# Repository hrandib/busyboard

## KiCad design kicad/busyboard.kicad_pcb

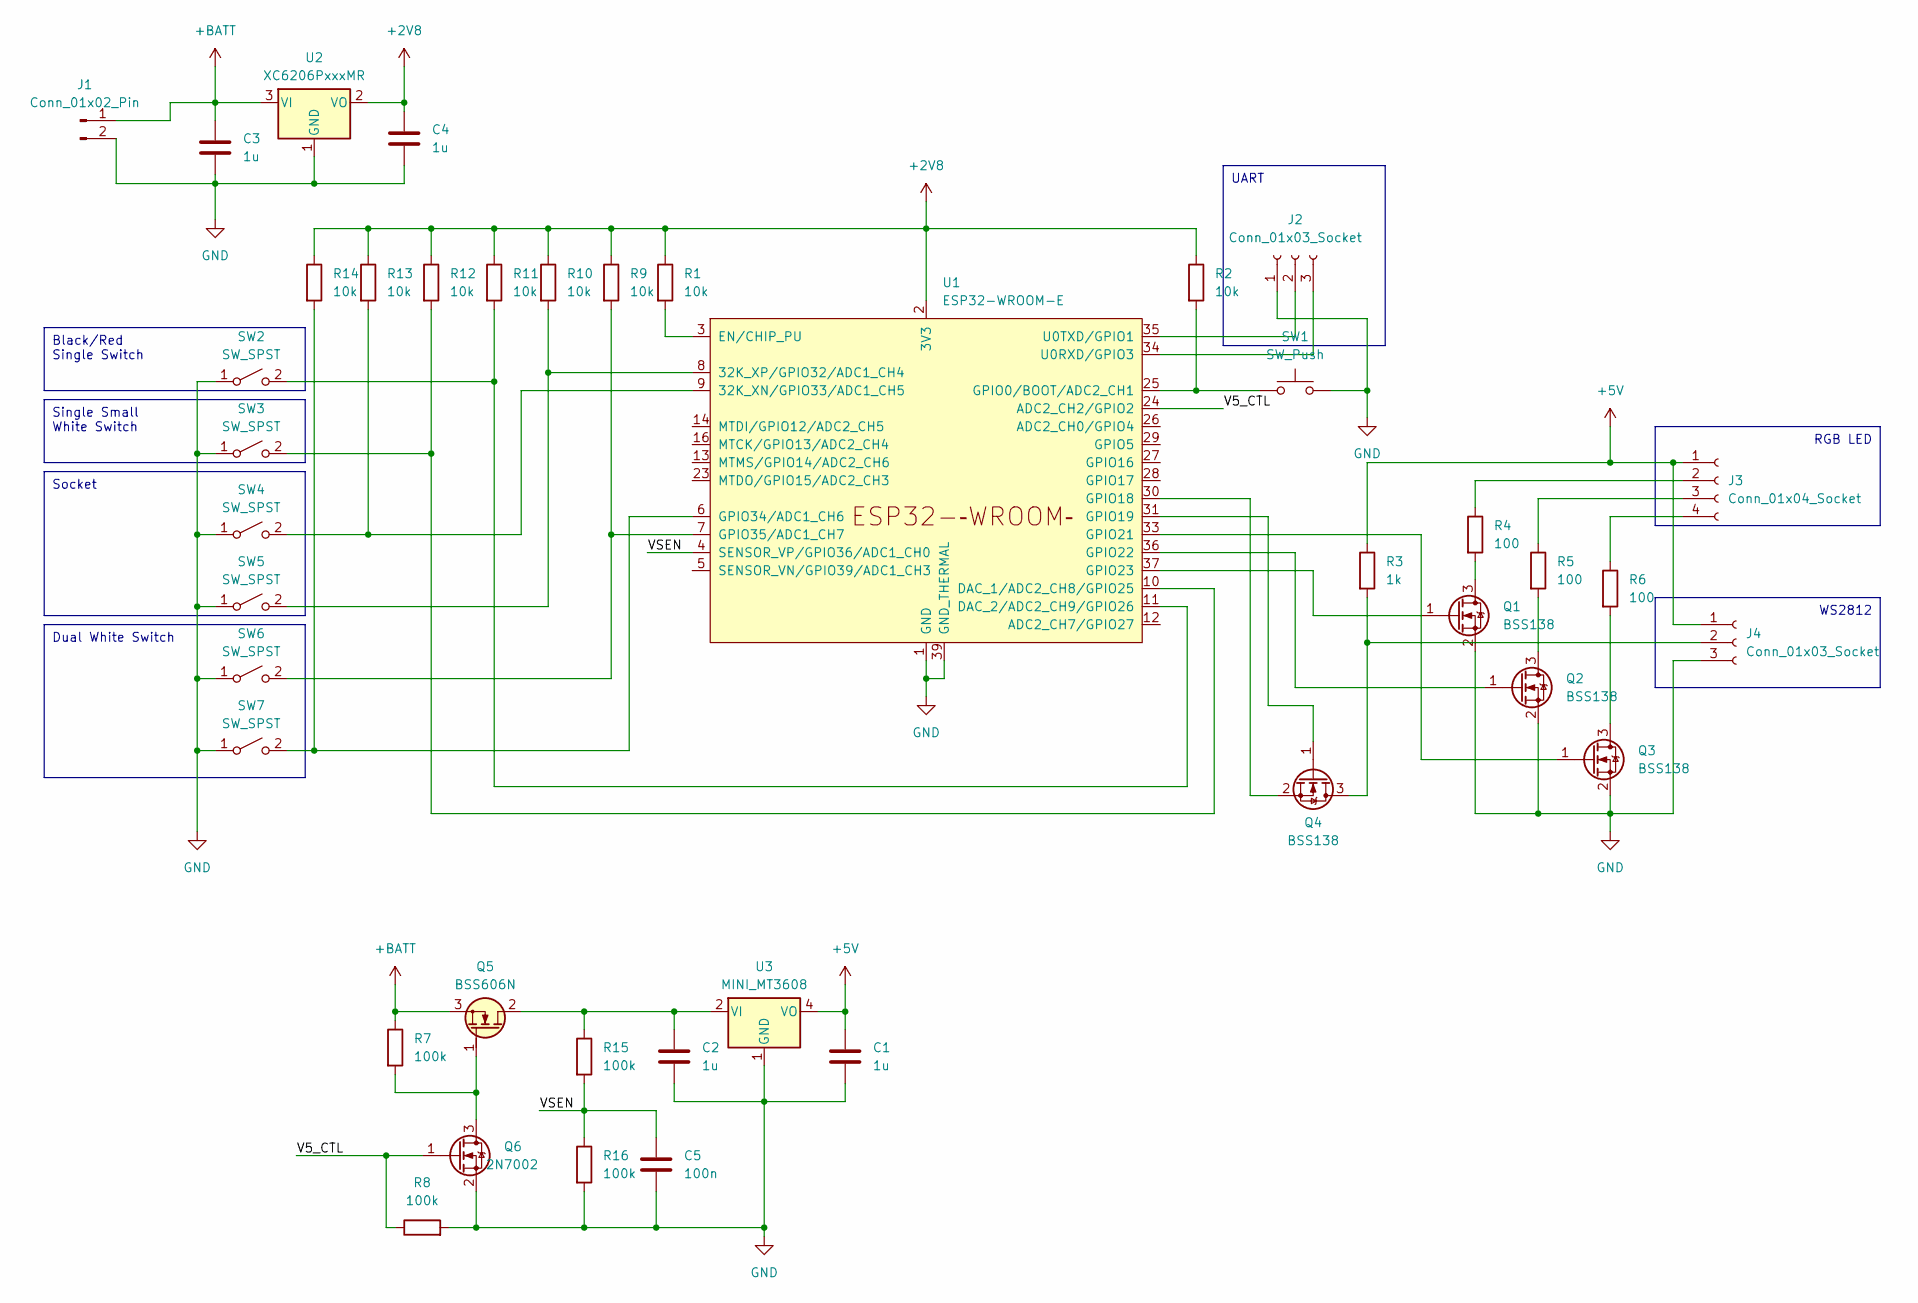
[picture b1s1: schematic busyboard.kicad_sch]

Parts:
C1, C2, C3, C4: 1u; C_0805_2012Metric
C5: 100n; C_0805_2012Metric
J1: Conn_01x02_Pin; PinHeader_1x02_P2.54mm_Vertical
J2, J4: Conn_01x03_Socket; PinHeader_1x03_P2.54mm_Vertical
J3: Conn_01x04_Socket; PinHeader_1x04_P2.54mm_Vertical
Q1, Q2, Q3, Q4: BSS138; SOT-23
Q5: BSS606N; SOT-89-3
Q6: 2N7002; SOT-23
R1, R2, R9, R10, R11, R12, R13, R14: 10k; R_0805_2012Metric
R3: 1k; R_0805_2012Metric
R4, R5, R6: 100; R_0805_2012Metric
R7, R8, R15, R16: 100k; R_0805_2012Metric
SW1: SW_Push; PinHeader_1x02_P2.54mm_Vertical
SW2, SW3, SW4, SW5, SW6, SW7: SW_SPST; PinHeader_1x02_P2.54mm_Vertical
U1: ESP32-WROOM-E; ESP32-WROOM-32E
U2: XC6206PxxxMR; SOT-23-3
U3: MINI_MT3608

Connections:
+2V8: C4.1, R1.1, R2.1, R9.1, R10.1, R11.1, R12.1, R13.1, R14.1, U1.2 (3V3), U2.2 (VO)
+5V: C1.1, J3.1, J4.1, R3.1, U3.4 (VO)
+BATT: C3.1, J1.1, Q5.3 (S), R7.1, U2.3 (VI)
/V5_CTL: Q6.1 (G), R8.1, U1.24 (ADC2_CH2/GPIO2)
/VSEN: C5.1, R15.2, R16.1, U1.4 (SENSOR_VP/GPIO36/ADC1_CH0)
GND: C1.2, C2.2, C3.2, C4.2, C5.2, J1.2, J2.1, J4.3, Q1.2 (S), Q2.2 (S), Q3.2 (S), Q6.2 (S), R8.2, R16.2, SW1.2, SW2.1 (A), SW3.1 (A), SW4.1 (A), SW5.1 (A), SW6.1 (A), SW7.1 (A), U1.1 (GND), U1.15 (GND), U1.38 (GND), U1.39 (GND_THERMAL), U2.1 (GND), U3.1 (GND), U3.3 (GND)
unnamed: J2.2, U1.35 (U0TXD/GPIO1)
unnamed: J2.3, U1.34 (U0RXD/GPIO3)
unnamed: J3.2, R4.1
unnamed: J3.3, R5.1
unnamed: J3.4, R6.1
unnamed: J4.2, Q4.3 (D), R3.2
unnamed: Q1.3 (D), R4.2
unnamed: Q1.1 (G), U1.37 (GPIO23)
unnamed: Q2.3 (D), R5.2
unnamed: Q2.1 (G), U1.36 (GPIO22)
unnamed: Q3.3 (D), R6.2
unnamed: Q3.1 (G), U1.33 (GPIO21)
unnamed: Q4.1 (G), U1.31 (GPIO19)
unnamed: Q4.2 (S), U1.30 (GPIO18)
unnamed: C2.1, Q5.2 (D), R15.1, U3.2 (VI)
unnamed: Q5.1 (G), Q6.3 (D), R7.2
unnamed: R11.2, SW2.2 (B), U1.11 (DAC_2/ADC2_CH9/GPIO26)
unnamed: R12.2, SW3.2 (B), U1.10 (DAC_1/ADC2_CH8/GPIO25)
unnamed: R13.2, SW4.2 (B), U1.9 (32K_XN/GPIO33/ADC1_CH5)
unnamed: R10.2, SW5.2 (B), U1.8 (32K_XP/GPIO32/ADC1_CH4)
unnamed: R9.2, SW6.2 (B), U1.7 (GPIO35/ADC1_CH7)
unnamed: R14.2, SW7.2 (B), U1.6 (GPIO34/ADC1_CH6)
unnamed: R1.2, U1.3 (EN/CHIP_PU)
unnamed: R2.2, SW1.1, U1.25 (GPIO0/BOOT/ADC2_CH1)

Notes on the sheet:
Black/Red Single Switch
UART
RGB LED
Dual White Switch
Single Small White Switch
WS2812
Socket

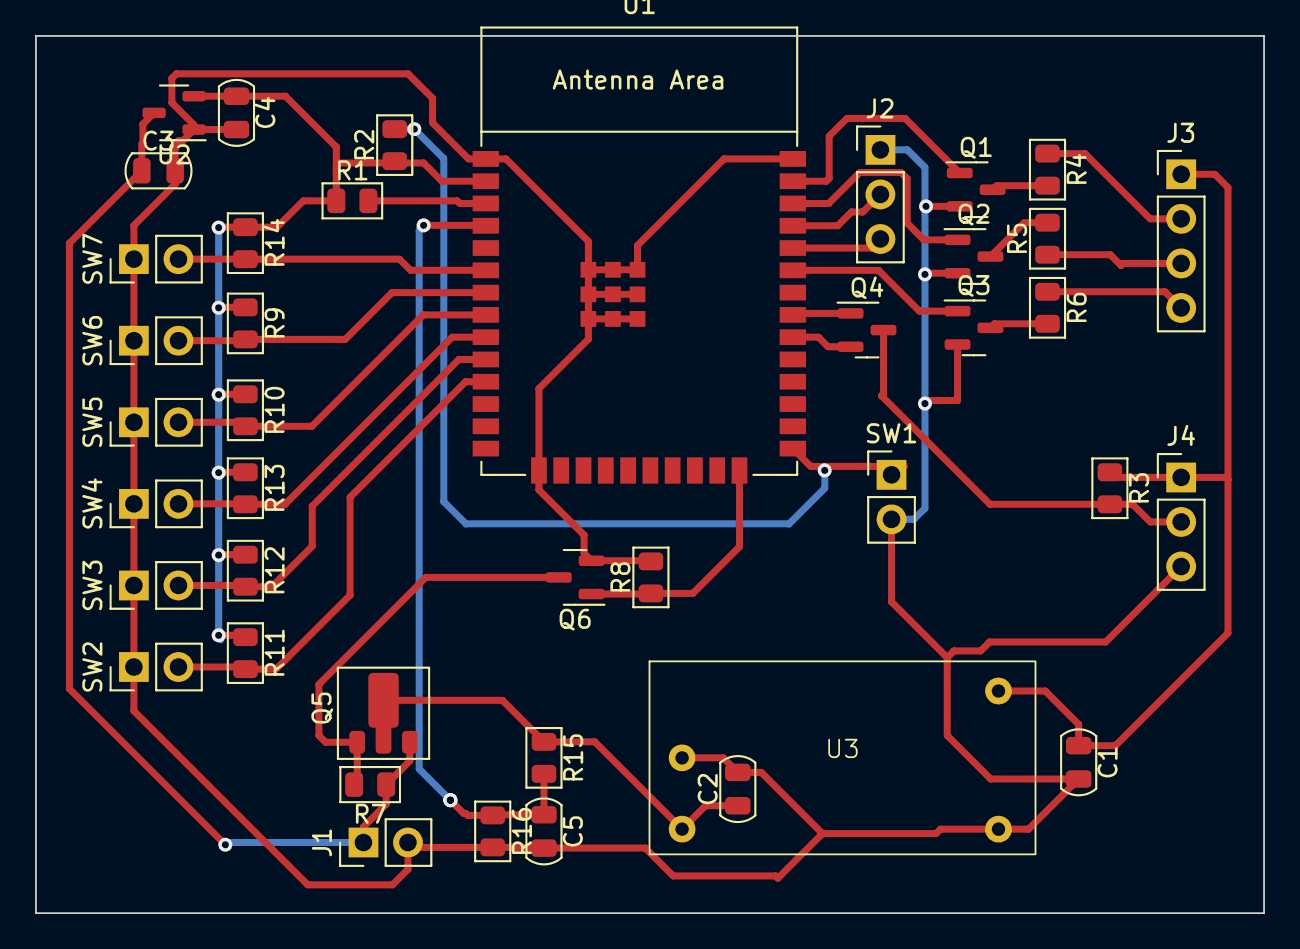
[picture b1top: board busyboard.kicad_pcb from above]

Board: 2 copper layers, 70.0 x 50.0 mm, 41 parts (0 on the bottom side), 30 nets.

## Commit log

2024-03-09 Add tasmota decode-config backup
